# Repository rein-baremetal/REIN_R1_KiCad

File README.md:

# REIN_R1 Hardware Design (KiCad 8.0+)

Welcome to the **REIN_R1** open-source PCB hardware project, part of the [REIN Baremetal](https://github.com/rein-baremetal) organization!

REIN_R1 is a multi-controller embedded development board built specifically for baremetal development, dual-architecture real-time control, and high-reliability embedded system experiments.

---

## What Makes REIN_R1 Stand Out?

Unlike standard single-SoC maker boards or basic evaluation kits, REIN_R1 combines high-performance coprocessing, rich peripheral interfacing, and power flexibility on a single compact 4-layer PCB:

* **Dual Microcontroller Co-Processing Architecture:** Integrates dual MCUs on-board to allow simultaneous execution of dedicated real-time control loops alongside higher-level communication and application tasks.
* **On-Board High-Speed QSPI Storage:** Dedicated QSPI flash interface configured for fast memory-mapped execution (XIP) and rapid firmware assets retrieval.
* **Integrated Hardware USB Hub:** Built-in multi-port USB hub logic eliminates external debug adapters, handling simultaneous programming, serial telemetry, and peripheral expansion over a single USB-C connection.
* **Robust Multi-Rail Power Management:** Features protected power input, integrated buck regulation, dedicated low-noise analog power paths (`3V3_A`), and smart battery/line switching (`VSYS`, `VIN`, `VBAT`).
* **Flexible Expansion & Communication:** Exposes dedicated SPI, I2C, UART, ADC channels, and GPIO arrays directly mapped for fast baremetal driver development without hardware bottlenecks.

---

## Current PCB Status

- **Schematic (`REIN_R1.kicad_sch`):** 100% Complete & Verified
- **Footprints & Symbol Libraries:** Custom library included (`REIN.kicad_sym`, `REIN.pretty/`)
- **Component Placement (`REIN_R1.kicad_pcb`):** 100% Complete
- **Routing:** **In Progress (Help Needed!)**

We are seeking open-source collaborators, hardware engineers, and layout enthusiasts to help route the remaining traces and achieve a 100% routed board that passes KiCad DRC with zero errors.

---

## Technical Specifications & Constraints

- **Board Layers:** 4 Layers (`F.Cu`, `In1.Cu` - GND, `In2.Cu` - Power Fills, `B.Cu`)
- **Default Track Width:** 0.20 mm (8 mil)
- **Default Track Clearance:** 0.20 mm (8 mil)
- **Minimum SMD Clearance:** 0.05 mm
- **Via Drill/Size:** Standard 0.3 mm / 0.6 mm

### Critical Routing Guidelines
1. **USB Differential Pairs (`/USB_DM_*`, `/USB_DP_*`):** Keep trace lengths matched and route as 90 Ω differential pairs. Minimize layer changes.
2. **QSPI Lines (`/QSPI_SCLK_*`, `/QSPI_SD0_*` to `/QSPI_SD3_*`, `/QSPI_SS_*`):** Length-match bus signals where feasible between MCU and flash storage. Keep tracks direct.
3. **Oscillator Traces (`/XIN_*`, `/XOUT_*`):** Keep routes as short as possible and isolate with ground pour fills.
4. **Power & Ground (`/GND`, `/3V3`, `/5V`, `/VIN`, `/VSYS`):** Ensure `In1.Cu` and `In2.Cu` ground planes maintain continuous connectivity without creating starved thermal islands on power/GND pads. Recalculate filled zones (`Ctrl + B`) after routing.

---

## How to Collaborate & Route

You can participate using either **KiCad PCB Editor** or **Freerouting**:

### Option A: Interactive Routing in KiCad
1. Clone or fork this repository:
   ```bash
   git clone https://github.com/rein-baremetal/REIN_R1_KiCad.git

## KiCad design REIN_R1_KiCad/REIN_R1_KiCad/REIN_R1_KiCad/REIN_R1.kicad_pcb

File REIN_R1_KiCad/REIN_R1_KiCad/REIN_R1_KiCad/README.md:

## Files
REIN_R1.kicad_pro / .kicad_sch / .kicad_pcb, REIN.kicad_sym (+ sym-lib-table), REIN.pretty (+ fp-lib-table), BOM, net table, GPIO map, tools/gen.py

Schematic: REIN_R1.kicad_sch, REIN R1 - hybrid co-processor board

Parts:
BT1: CR1220; BatteryHolder_Keystone_3034_1x20mm
C1, C4, C5, C11, C15, C18, C19, C20, C21, C22, C23, C24, C25, C26, C27, C30, C31, C34, C35, C36, C37, C38, C39, C40, C41, C42, C43, C46, C47, C49, C54, C56, C57, C58, C59, C60, C62, C63, C64, C65, C66: 100n; C_0402_1005Metric
C2, C3, C7, C8, C9, C10, C12, C51, C55: 10u; C_0402_1005Metric
C6, C13, C14, C48: 22u; C_0402_1005Metric
C16, C17, C32, C33: 15p; C_0402_1005Metric
C28, C29, C44, C45, C50, C52, C53, C61: 1u; C_0402_1005Metric
D1: SMBJ24A; D_SMB
D2: SMBJ33A; D_SMB
D3, D4: SS34; D_SMA
D5, D6, D7: SS14; D_SOD-123
D8: CHG (red); LED_0603_1608Metric
D9: PWR (green); LED_0603_1608Metric
D10: BT / USER (blue); LED_0603_1608Metric
DZ1: BZX84-10V; D_SOD-123
F1: PTC 2A; Fuse_1206_3216Metric
FB1: Ferrite 600R; R_0402_1005Metric
J1: USB-C (HRO TYPE-C-31-M-12); USB_C_Receptacle_HRO_TYPE-C-31-M-12
J2: DC IN 6-36V; TerminalBlock_bornier-2_P5.08mm
J3: LiPo (JST-PH); JST_PH_S2B-PH-SM4-TB_1x02-1MP_P2.00mm_Horizontal
J4: microSD (Hirose DM3AT); microSD_HC_Hirose_DM3AT-SF-PEJM5
J5: OLED 0.91in (GND VCC SCL SDA); PinHeader_1x04_P2.54mm_Vertical
J6, J7: Qwiic (SH 4-pin); JST_SH_SM04B-SRSS-TB_1x04-1MP_P1.00mm_Horizontal
J8: Grove I2C (PH 4-pin); JST_PH_B4B-PH-K_1x04_P2.00mm_Vertical
J9: Pi 40-pin HAT socket; PinSocket_2x20_P2.54mm_Vertical
J10: EEPROM WP jumper (short = writable); PinHeader_1x02_P2.54mm_Vertical
J11: SWD (CLK DIO GND RUN 3V3); PinHeader_1x05_P2.54mm_Vertical
J12: Debug UART (GND TX RX); PinHeader_1x03_P2.54mm_Vertical
J13: ESP UART (GND TX RX 3V3); PinHeader_1x04_P2.54mm_Vertical
J14: Breadboard RP2040 5V I/O (22-27, 5V, GND); PinHeader_1x08_P2.54mm_Vertical
J15: Breadboard ESP32 5V I/O 1-8; PinHeader_1x08_P2.54mm_Vertical
J16: Breadboard power (5V 3V3 GND GND); PinHeader_1x04_P2.54mm_Vertical
J17: ADC in (AIN0-3, GND, 3V3_A); PinHeader_1x06_P2.54mm_Vertical
J18: DAC out (AOUT, GND); PinHeader_1x02_P2.54mm_Vertical
L1: 10u; L_1210_3225Metric
L2: 2.2u; L_Taiyo-Yuden_NR-40xx
Q1: P-MOSFET 40V (reverse protect); SOT-23
R1, R2: 5.1k; R_0402_1005Metric; not fitted
R3, R5, R13, R14: 100k; R_0402_1005Metric
R4: 732k; R_0402_1005Metric
R6: 2k; R_0402_1005Metric
R7, R10, R11, R12, R19, R20, R27, R33, R34, R35, R36: 1k; R_0402_1005Metric
R8: 1M; R_0402_1005Metric
R9: 221k; R_0402_1005Metric
R15, R16: 2.2k; R_0402_1005Metric
R17, R18, R25, R26, R28, R29, R30, R31, R32, R40, R41: 10k; R_0402_1005Metric
R21, R22, R23, R24: 27R; R_0402_1005Metric
R37: 100R; R_0402_1005Metric
R38, R39: 4.7k; R_0402_1005Metric
RSH1: 20m shunt; R_1206_3216Metric
SW1, SW3: BOOTSEL; SW_SPST_TL3342
SW2: RESET; SW_SPST_TL3342
SW4: PROBE RESET; SW_SPST_TL3342
SW5: ESP RESET; SW_SPST_TL3342
SW6: ESP BOOT; SW_SPST_TL3342
U1, U3: RP2040; QFN-56-1EP_7x7mm_P0.4mm_EP3.2x3.2mm
U2: W25Q128JVSIQ; SOIC-8_5.23x5.23mm_P1.27mm
U4: W25Q16JV; SOIC-8_5.23x5.23mm_P1.27mm
U5: ESP32-S3-WROOM-1-N8; ESP32-S3-WROOM-1
U7: Wide-in buck 5V (TPS54202-class); SOT-23-6
U8: INA226AIDGSR; VSSOP-10_3x3mm_P0.5mm
U9: MCP73831T-2ACI/OT; SOT-23-5
U10: MAX17048G+T10; DFN-8-1EP_2x2mm_P0.5mm_EP0.7x1.3mm
U11: TLV62569DBV; SOT-23-5
U12: REF3033 (3.3V ref); SOT-23
U13: ADS1115IDGSR; VSSOP-10_3x3mm_P0.5mm
U14: MCP4725A1T-E/CH; SOT-23-6
U15: ATECC608B-SSHDA; SOIC-8_3.9x4.9mm_P1.27mm
U16: DS3231SN#; SOIC-16W_7.5x10.3mm_P1.27mm
U17: USB2.0 4-port hub (CH334-class); QFN-24-1EP_4x4mm_P0.5mm_EP2.6x2.6mm
U18: STUSB4500 (QFN-24); QFN-24-1EP_4x4mm_P0.5mm_EP2.6x2.6mm
U19: USBLC6-2SC6; SOT-23-6
U20: TPS22918 (Qwiic switch); SOT-23-6
U21: CAT24C32WI (HAT ID EEPROM); SOIC-8_3.9x4.9mm_P1.27mm
U22, U23: TXS0108EPWR; TSSOP-20_4.4x6.5mm_P0.65mm
Y1, Y2: 12MHz; Crystal_SMD_3225-4Pin_3.2x2.5mm

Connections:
/1V1_P: C42.1, C43.1, C45.1, U3.23 (DVDD), U3.45 (VREG_VOUT), U3.50 (DVDD)
/1V1_T: C26.1, C27.1, C29.1, U1.23 (DVDD), U1.45 (VREG_VOUT), U1.50 (DVDD)
/3V3: C1.1, C5.1, C13.1, C14.1, C15.1, C18.1, C19.1, C20.1, C21.1, C22.1, C23.1, C24.1, C25.1, C28.1, C31.1, C34.1, C35.1, C36.1, C37.1, C38.1, C39.1, C40.1, C41.1, C44.1, C46.1, C47.1, C48.1, C49.1, C51.1, C57.1, C58.1, C60.1, C62.1, C63.1, C65.1, FB1.1, J4.4 (VDD), J5.2 (VCC), J11.5 (3V3), J13.4 (3V3), J16.2 (3V3), L2.2, R8.1, R10.1, R15.2, R16.2, R17.2, R18.2, R25.1, R26.1, R28.2, R29.2, R30.2, R31.2, R32.2, R40.2, R41.2, U1.1 (IOVDD), U1.10 (IOVDD), U1.22 (IOVDD), U1.33 (IOVDD), U1.42 (IOVDD), U1.43 (ADC_AVDD), U1.44 (VREG_VIN), U1.48 (USB_VDD), U1.49 (IOVDD), U2.8 (VCC), U3.1 (IOVDD), U3.10 (IOVDD), U3.22 (IOVDD), U3.33 (IOVDD), U3.42 (IOVDD), U3.43 (ADC_AVDD), U3.44 (VREG_VIN), U3.48 (USB_VDD), U3.49 (IOVDD), U4.8 (VCC), U5.2 (3V3), U8.6 (VS), U15.8 (VCC), U16.2 (VCC), U17.11 (VDD33), U18.11 (VDD), U20.1 (VIN), U21.8 (VCC), U22.2 (VCCA), U23.2 (VCCA)
/3V3_A: C55.1, C56.1, FB1.2, J17.6 (3V3A), U13.8 (VDD)
/5V: C7.1, C8.1, C9.1, C64.1, C66.1, D5.2 (A), D7.1 (K), J14.7 (5V), J16.1 (5V), R7.1, RSH1.2, U8.8 (VBUS), U8.9 (IN-), U9.4 (VDD), U22.19 (VCCB), U23.19 (VCCB)
/5V_BUCK: C6.1, F1.1, L1.2, R4.1
/5V_F: F1.2, RSH1.1, U8.10 (IN+)
/AIN0: R33.2, U13.4 (AIN0)
/AIN0_H: J17.1 (AIN0), R33.1
/AIN1: R34.2, U13.5 (AIN1)
/AIN1_H: J17.2 (AIN1), R34.1
/AIN2: R35.2, U13.6 (AIN2)
/AIN2_H: J17.3 (AIN2), R35.1
/AIN3: R36.2, U13.7 (AIN3)
/AIN3_H: J17.4 (AIN3), R36.1
/AOUT_H: J18.1 (AOUT), R37.2
/BB_22: J14.1 (IO22), U22.20 (B1)
/BB_23: J14.2 (IO23), U22.18 (B2)
/BB_24: J14.3 (IO24), U22.17 (B3)
/BB_25: J14.4 (IO25), U22.16 (B4)
/BB_26: J14.5 (IO26), U22.15 (B5)
/BB_27: J14.6 (IO27), U22.14 (B6)
/BE_1: J15.1 (E1), U23.20 (B1)
/BE_2: J15.2 (E2), U23.18 (B2)
/BE_3: J15.3 (E3), U23.17 (B3)
/BE_4: J15.4 (E4), U23.16 (B4)
/BE_5: J15.5 (E5), U23.15 (B5)
/BE_6: J15.6 (E6), U23.14 (B6)
/BE_7: J15.7 (E7), U23.13 (B7)
/BE_8: J15.8 (E8), U23.12 (B8)
/BK3_FB: R8.2, R9.1, U11.5 (FB)
/BK3_SW: L2.1, U11.3 (SW)
/BK5_BST: C4.1, U7.6 (BST)
/BK5_FB: R4.2, R5.1, U7.4 (FB)
/BK5_SW: C4.2, L1.1, U7.2 (SW)
/BOOTR_P: R20.2, SW3.1
/BOOTR_T: R12.2, SW1.1
/CC1: J1.A5, R1.1, U18.1 (CC1)
/CC2: J1.B5, R2.1, U18.2 (CC2)
/CHG_LED_A: D8.2 (A), R7.2
/CHG_PROG: R6.1, U9.5 (PROG)
/CHG_STAT: D8.1 (K), U9.1 (STAT)
/DAC_OUT: R37.1, U14.1 (VOUT)
/DBG_RX: J12.3 (RX), U1.3 (GPIO1), U3.6 (GPIO4)
/DBG_TX: J12.2 (TX), U1.2 (GPIO0), U3.7 (GPIO5)
/EE_WP: J10.1 (WP), R40.1, U21.7 (WP)
/ESP_B1: U5.4 (IO4), U23.1 (A1)
/ESP_B2: U5.5 (IO5), U23.3 (A2)
/ESP_B3: U5.6 (IO6), U23.4 (A3)
/ESP_B4: U5.7 (IO7), U23.5 (A4)
/ESP_B5: U5.8 (IO15), U23.6 (A5)
/ESP_B6: U5.9 (IO16), U23.7 (A6)
/ESP_B7: U5.10 (IO17), U23.8 (A7)
/ESP_B8: U5.11 (IO18), U23.9 (A8)
/ESP_CS: U1.28 (GPIO17), U5.18 (IO10)
/ESP_DRDY: U1.18 (GPIO15), U5.17 (IO9)
/ESP_EN: C50.1, R25.2, SW5.1, U1.31 (GPIO20), U5.3 (EN)
/ESP_HS: U1.17 (GPIO14), U5.22 (IO14)
/ESP_IO0: R26.2, SW6.1, U1.32 (GPIO21), U5.27 (IO0)
/ESP_MISO: U1.27 (GPIO16), U5.21 (IO13)
/ESP_MOSI: U1.30 (GPIO19), U5.19 (IO11)
/ESP_RXD0: J13.3 (RX), U5.36 (RXD0_IO44)
/ESP_SCK: U1.29 (GPIO18), U5.20 (IO12)
/ESP_TXD0: J13.2 (TX), U5.37 (TXD0_IO43)
/GND: BT1.2 (-), C1.2, C2.2, C3.2, C5.2, C6.2, C7.2, C8.2, C9.2, C10.2, C11.2, C12.2, C13.2, C14.2, C15.2, C16.2, C17.2, C18.2, C19.2, C20.2, C21.2, C22.2, C23.2, C24.2, C25.2, C26.2, C27.2, C28.2, C29.2, C30.2, C31.2, C32.2, C33.2, C34.2, C35.2, C36.2, C37.2, C38.2, C39.2, C40.2, C41.2, C42.2, C43.2, C44.2, C45.2, C46.2, C47.2, C48.2, C49.2, C50.2, C51.2, C52.2, C53.2, C54.2, C55.2, C56.2, C57.2, C58.2, C59.2, C60.2, C61.2, C62.2, C63.2, C64.2, C65.2, C66.2, D1.2 (A), D2.2 (A), D9.1 (K), D10.1 (K), J1.A1, J1.A12, J1.B1, J1.B12, J1.S1, J2.2 (GND), J3.2 (-), J3.MP, J4.6 (VSS), J4.10 (SH1), J4.11 (SH2), J5.1 (GND), J6.1 (GND), J6.MP, J7.1 (GND), J7.MP, J8.4 (GND), J9.6, J9.9, J9.14, J9.20, J9.25, J9.30, J9.34, J9.39, J10.2 (GND), J11.3 (GND), J12.1 (GND), J13.1 (GND), J14.8 (GND), J16.3 (GND), J16.4 (GND), J17.5 (GND), J18.2 (GND), R1.2, R2.2, R3.2, R5.2, R6.2, R9.2, R14.2, SW1.2, SW2.2, SW3.2, SW4.2, SW5.2, SW6.2, U1.19 (TESTEN), U1.57 (GND), U2.4 (GND), U3.19 (TESTEN), U3.57 (GND), U4.4 (GND), U5.1 (GND), U5.40 (GND), U5.41 (GND_EP), U7.1 (GND), U8.1 (A1), U8.2 (A0), U8.7 (GND), U9.2 (VSS), U10.3 (GND), U10.4 (QSTRT), U10.8 (CTG), U10.9 (EP), U11.2 (GND), U12.3 (GND), U13.1 (ADDR), U13.3 (GND), U14.2 (VSS), U14.6 (A0), U15.4 (GND), U16.13 (GND), U17.24 (GND), U17.25 (EP), U18.8 (ADDR0), U18.9 (ADDR1), U18.10 (RESET), U18.24 (GND), U18.25 (EP), U19.2 (GND), U20.2 (GND), U21.1 (A0), U21.2 (A1), U21.3 (A2), U21.4 (VSS), U22.11 (GND), U23.11 (GND), Y1.2 (GND), Y1.4 (GND), Y2.2 (GND), Y2.4 (GND)
/HUB_DM1: R24.1, U17.4 (DM1)
/HUB_DM2: R22.1, U17.6 (DM2)
/HUB_DP1: R23.1, U17.3 (DP1)
/HUB_DP2: R21.1, U17.5 (DP2)
/I2CA_SCL: J5.3 (SCL), R16.1, U1.7 (GPIO5), U8.5 (SCL), U10.6 (SCL), U13.10 (SCL), U14.5 (SCL), U15.6 (SCL), U16.16 (SCL), U18.6 (SCL)
/I2CA_SDA: J5.4 (SDA), R15.1, U1.6 (GPIO4), U8.4 (SDA), U10.5 (SDA), U13.9 (SDA), U14.4 (SDA), U15.5 (SDA), U16.15 (SDA), U18.5 (SDA)
/I2CQ_SCL: J6.4 (SCL), J7.4 (SCL), J8.1 (SCL), R39.1, U1.5 (GPIO3)
/I2CQ_SDA: J6.3 (SDA), J7.3 (SDA), J8.2 (SDA), R38.1, U1.4 (GPIO2)
/ID_SC: J9.28, U21.6 (SCL)
/ID_SD: J9.27, U21.5 (SDA)
/INT_PWR: R17.1, U1.8 (GPIO6), U8.3 (ALERT), U10.7 (ALRT), U18.7 (ALERT)
/LED_USR: R27.1, U5.38 (IO2)
/LED_USR_A: D10.2 (A), R27.2
/PI_5V: D7.2 (A), J9.2, J9.4
/PI_CE0: J9.24, U1.16 (GPIO13)
/PI_MISO: J9.21, U1.14 (GPIO11)
/PI_MOSI: J9.19, U1.15 (GPIO12)
/PI_RXD: J9.10, U1.11 (GPIO8)
/PI_SCLK: J9.23, U1.13 (GPIO10)
/PI_TXD: J9.8, U1.12 (GPIO9)
/PWR_LED_A: D9.2 (A), R10.2
/Q1_G: DZ1.2 (A), Q1.1 (G), R3.1
/Q3V3: C61.1, J6.2 (3V3), J7.2 (3V3), J8.3 (VCC), R38.2, R39.2, U20.6 (VOUT)
/QSPI_SCLK_P: U3.52 (QSPI_SCLK), U4.6 (CLK)
/QSPI_SCLK_T: U1.52 (QSPI_SCLK), U2.6 (CLK)
/QSPI_SD0_P: U3.53 (QSPI_SD0), U4.5 (DI/IO0)
/QSPI_SD0_T: U1.53 (QSPI_SD0), U2.5 (DI/IO0)
/QSPI_SD1_P: U3.55 (QSPI_SD1), U4.2 (DO/IO1)
/QSPI_SD1_T: U1.55 (QSPI_SD1), U2.2 (DO/IO1)
/QSPI_SD2_P: U3.54 (QSPI_SD2), U4.3 (WP#/IO2)
/QSPI_SD2_T: U1.54 (QSPI_SD2), U2.3 (WP#/IO2)
/QSPI_SD3_P: U3.51 (QSPI_SD3), U4.7 (HOLD#/IO3)
/QSPI_SD3_T: U1.51 (QSPI_SD3), U2.7 (HOLD#/IO3)
/QSPI_SS_P: R20.1, U3.56 (QSPI_SS), U4.1 (CS#)
/QSPI_SS_T: R12.1, U1.56 (QSPI_SS), U2.1 (CS#)
/QWIIC_EN: U1.40 (GPIO28_ADC2), U20.3 (ON)
/RP_IO22: U1.34 (GPIO22), U22.1 (A1)
/RP_IO23: U1.35 (GPIO23), U22.3 (A2)
/RP_IO24: U1.36 (GPIO24), U22.4 (A3)
/RP_IO25: U1.37 (GPIO25), U22.5 (A4)
/RP_IO26: U1.38 (GPIO26_ADC0), U22.6 (A5)
/RP_IO27: U1.39 (GPIO27_ADC1), U22.7 (A6)
/RTC_INT: R18.1, U1.9 (GPIO7), U16.3 (INT#/SQW)
/RTC_VBAT: BT1.1 (+), C59.1, U16.14 (VBAT)
/RUN_P: SW4.1, U3.26 (RUN)
/RUN_T: J11.4 (RUN), SW2.1, U1.26 (RUN), U3.3 (GPIO1)
/SD_CLK: J4.5 (CLK), U5.33 (IO40)
/SD_CMD: J4.3 (CMD), R32.1, U5.32 (IO39)
/SD_D0: J4.7 (DAT0), R28.1, U5.34 (IO41)
/SD_D1: J4.8 (DAT1), R29.1, U5.35 (IO42)
/SD_D2: J4.1 (DAT2), R30.1, U5.31 (IO38)
/SD_D3: J4.2 (DAT3/CD), R31.1, U5.23 (IO21)
/SWCLK: J11.1 (SWCLK), U1.24 (SWCLK), U3.4 (GPIO2)
/SWDIO: J11.2 (SWDIO), U1.25 (SWD), U3.5 (GPIO3)
/TXS_OE: R41.1, U22.10 (OE), U23.10 (OE)
/USB_DM_C: J1.A7, J1.B7, U17.2 (UP_DM), U19.3 (IO2), U19.4 (IO2b)
/USB_DP_C: J1.A6, J1.B6, U17.1 (UP_DP), U19.1 (IO1), U19.6 (IO1b)
/USB_E_DM: U5.13 (IO19_USB_DM), U17.8 (DM3)
/USB_E_DP: U5.14 (IO20_USB_DP), U17.7 (DP3)
/USB_P_DM: R22.2, U3.46 (USB_DM)
/USB_P_DP: R21.2, U3.47 (USB_DP)
/USB_T_DM: R24.2, U1.46 (USB_DM)
/USB_T_DP: R23.2, U1.47 (USB_DP)
/VBAT: C10.1, C11.1, D6.2 (A), J3.1 (+), U9.3 (VBAT), U10.1 (CELL), U10.2 (VDD)
/VBUS: D1.1 (K), D3.2 (A), J1.A4, J1.A9, J1.B4, J1.B9, U17.12 (VBUS_DET), U18.3 (VBUS_SENSE), U19.5 (VBUS)
/VDC_PROT: D4.2 (A), DZ1.1 (K), Q1.2 (S)
/VDC_RAW: D2.1 (K), J2.1 (VDC+), Q1.3 (D)
/VIN: C2.1, C3.1, D3.1 (K), D4.1 (K), U7.3 (VIN), U7.5 (EN)
/VREF_3V3: C53.1, C54.1, U12.2 (VOUT), U14.3 (VDD)
/VSYS: C12.1, C52.1, D5.1 (K), D6.1 (K), R13.1, U11.1 (EN), U11.4 (VIN), U12.1 (VIN)
/VSYS_SENSE: C30.1, R13.2, R14.1, U1.41 (GPIO29_ADC3)
/XIN_P: C32.1, U3.20 (XIN), Y2.1 (XIN)
/XIN_T: C16.1, U1.20 (XIN), Y1.1 (XIN)
/XOUT_P: R19.1, U3.21 (XOUT)
/XOUT_R_P: C33.1, R19.2, Y2.3 (XOUT)
/XOUT_R_T: C17.1, R11.2, Y1.3 (XOUT)
/XOUT_T: R11.1, U1.21 (XOUT)

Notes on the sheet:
1 USB-C + PD + hub
2 Power input + 5V
3 Charger, fuel gauge, 3V3
4 RP2040 target (main MCU)
5 RP2040 debug probe
6 USB hub + ESD
7 ESP32-S3 + microSD
8 Analog + secure + RTC
9 Bus A devices, Qwiic/Grove
10 Pi 5 HAT header + debug headers
11 Breadboard / level shifters
12 Power flags

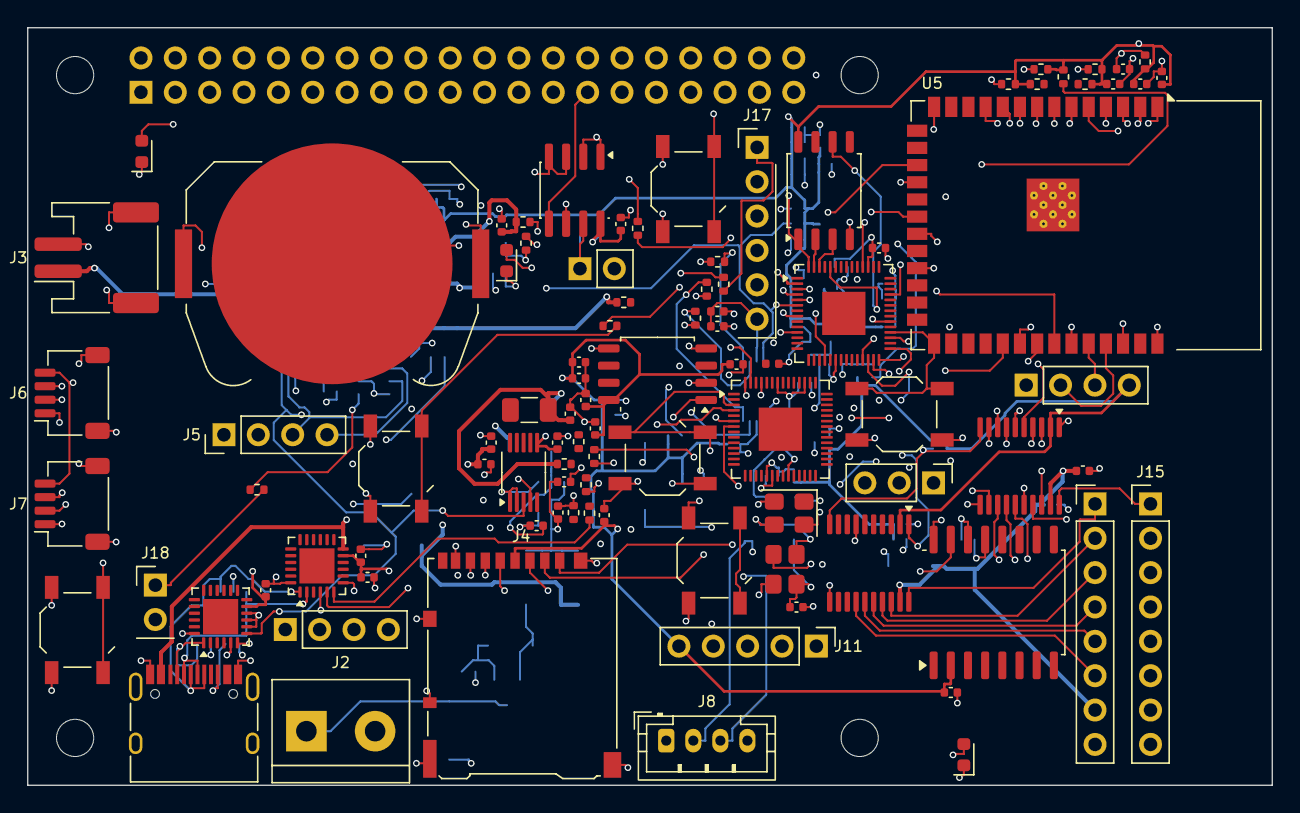
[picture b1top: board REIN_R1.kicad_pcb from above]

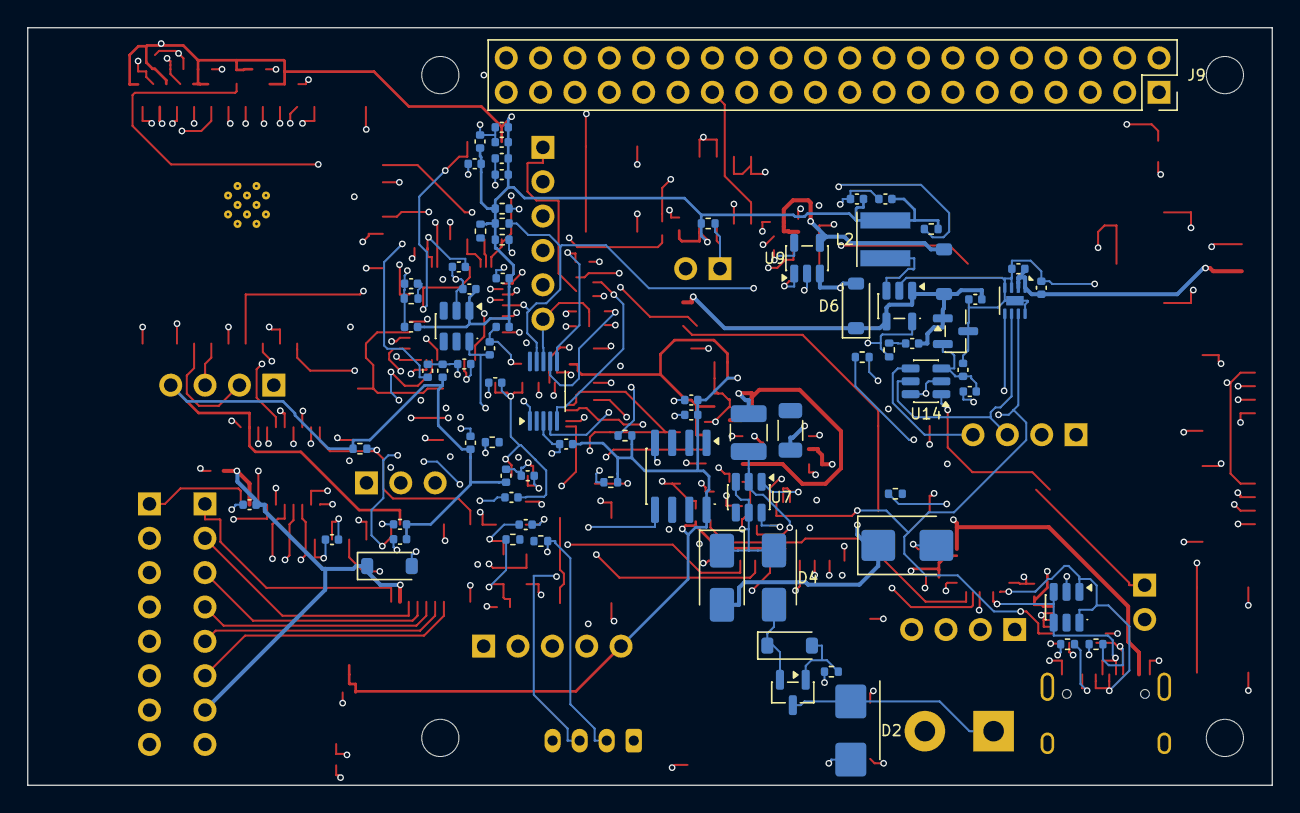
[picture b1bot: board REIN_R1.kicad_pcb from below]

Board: 4 copper layers, 92.0 x 56.0 mm, 177 parts (79 on the bottom side), 142 nets.

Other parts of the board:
H1, H2, H3, H4: MountingHole; MountingHole_2.75mm_M2.5_HAT

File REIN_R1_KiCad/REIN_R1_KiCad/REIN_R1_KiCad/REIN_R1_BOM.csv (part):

Ref,Value,Footprint,DNP,Confidence,Note
J1,USB-C (HRO TYPE-C-31-M-12),REIN:USB_C_Receptacle_HRO_TYPE-C-31-M-12,,ok,
R1,5.1k,Resistor_SMD:R_0402_1005Metric,yes,ok,Fit ONLY if PD controller U18 is removed
R2,5.1k,Resistor_SMD:R_0402_1005Metric,yes,ok,Fit ONLY if PD controller U18 is removed
D1,SMBJ24A,Diode_SMD:D_SMB,,ok,
U19,USBLC6-2SC6,Package_TO_SOT_SMD:SOT-23-6,,ok,
U18,STUSB4500 (QFN-24),Package_DFN_QFN:QFN-24-1EP_4x4mm_P0.5mm_EP2.6x2.6mm,,VERIFY,Generic pin order - replace with datasheet pinout
C1,100n,Capacitor_SMD:C_0402_1005Metric,,ok,
J2,DC IN 6-36V,REIN:TerminalBlock_bornier-2_P5.08mm,,ok,
D2,SMBJ33A,Diode_SMD:D_SMB,,ok,
Q1,P-MOSFET 40V (reverse protect),Package_TO_SOT_SMD:SOT-23,,ok,
R3,100k,Resistor_SMD:R_0402_1005Metric,,ok,
DZ1,BZX84-10V,Diode_SMD:D_SOD-123,,ok,
D3,SS34,Diode_SMD:D_SMA,,ok,
D4,SS34,Diode_SMD:D_SMA,,ok,
C2,10u,Capacitor_SMD:C_0402_1005Metric,,ok,
C3,10u,Capacitor_SMD:C_0402_1005Metric,,ok,
U7,Wide-in buck 5V (TPS54202-class),Package_TO_SOT_SMD:SOT-23-6,,VERIFY,Pin order from TPS54202 family - verify; check 36V rating of final part
C4,100n,Capacitor_SMD:C_0402_1005Metric,,ok,
L1,10u,Inductor_SMD:L_1210_3225Metric,,ok,
U8,INA226AIDGSR,REIN:VSSOP-10_3x3mm_P0.5mm,,ok,
C5,100n,Capacitor_SMD:C_0402_1005Metric,,ok,
R4,732k,Resistor_SMD:R_0402_1005Metric,,ok,
R5,100k,Resistor_SMD:R_0402_1005Metric,,ok,
C6,22u,Capacitor_SMD:C_0402_1005Metric,,ok,
F1,PTC 2A,Fuse:Fuse_1206_3216Metric,,ok,
RSH1,20m shunt,Resistor_SMD:R_1206_3216Metric,,ok,
D7,SS14,Diode_SMD:D_SOD-123,,ok,
C7,10u,Capacitor_SMD:C_0402_1005Metric,,ok,
C8,10u,Capacitor_SMD:C_0402_1005Metric,,ok,
U9,MCP73831T-2ACI/OT,Package_TO_SOT_SMD:SOT-23-5,,ok,
R6,2k,Resistor_SMD:R_0402_1005Metric,,ok,
C9,10u,Capacitor_SMD:C_0402_1005Metric,,ok,
C10,10u,Capacitor_SMD:C_0402_1005Metric,,ok,
R7,1k,Resistor_SMD:R_0402_1005Metric,,ok,
D8,CHG (red),LED_SMD:LED_0603_1608Metric,,ok,
J3,LiPo (JST-PH),Connector_JST:JST_PH_S2B-PH-SM4-TB_1x02-1MP_P2.00mm_Horizontal,,ok,
U10,MAX17048G+T10,REIN:DFN-8-1EP_2x2mm_P0.5mm_EP0.7x1.3mm,,VERIFY,Pin order from memory - verify against datasheet
C11,100n,Capacitor_SMD:C_0402_1005Metric,,ok,
D5,SS14,Diode_SMD:D_SOD-123,,ok,
D6,SS14,Diode_SMD:D_SOD-123,,ok,
C12,10u,Capacitor_SMD:C_0402_1005Metric,,ok,
U11,TLV62569DBV,Package_TO_SOT_SMD:SOT-23-5,,ok,
L2,2.2u,Inductor_SMD:L_Taiyo-Yuden_NR-40xx,,ok,
R8,1M,Resistor_SMD:R_0402_1005Metric,,ok,
R9,221k,Resistor_SMD:R_0402_1005Metric,,ok,
C13,22u,Capacitor_SMD:C_0402_1005Metric,,ok,
C14,22u,Capacitor_SMD:C_0402_1005Metric,,ok,
R10,1k,Resistor_SMD:R_0402_1005Metric,,ok,
D9,PWR (green),LED_SMD:LED_0603_1608Metric,,ok,
U1,RP2040,Package_DFN_QFN:QFN-56-1EP_7x7mm_P0.4mm_EP3.2x3.2mm,,ok,
U2,W25Q128JVSIQ,REIN:SOIC-8_5.23x5.23mm_P1.27mm,,ok,
C15,100n,Capacitor_SMD:C_0402_1005Metric,,ok,
Y1,12MHz,Crystal:Crystal_SMD_3225-4Pin_3.2x2.5mm,,ok,
R11,1k,Resistor_SMD:R_0402_1005Metric,,ok,
C16,15p,Capacitor_SMD:C_0402_1005Metric,,ok,
C17,15p,Capacitor_SMD:C_0402_1005Metric,,ok,
C18,100n,Capacitor_SMD:C_0402_1005Metric,,ok,
C19,100n,Capacitor_SMD:C_0402_1005Metric,,ok,
C20,100n,Capacitor_SMD:C_0402_1005Metric,,ok,
C21,100n,Capacitor_SMD:C_0402_1005Metric,,ok,
C22,100n,Capacitor_SMD:C_0402_1005Metric,,ok,
C23,100n,Capacitor_SMD:C_0402_1005Metric,,ok,
C24,100n,Capacitor_SMD:C_0402_1005Metric,,ok,
C25,100n,Capacitor_SMD:C_0402_1005Metric,,ok,
C26,100n,Capacitor_SMD:C_0402_1005Metric,,ok,
C27,100n,Capacitor_SMD:C_0402_1005Metric,,ok,
C28,1u,Capacitor_SMD:C_0402_1005Metric,,ok,
C29,1u,Capacitor_SMD:C_0402_1005Metric,,ok,
R12,1k,Resistor_SMD:R_0402_1005Metric,,ok,
SW1,BOOTSEL,Button_Switch_SMD:SW_SPST_TL3342,,ok,
SW2,RESET,Button_Switch_SMD:SW_SPST_TL3342,,ok,
R13,100k,Resistor_SMD:R_0402_1005Metric,,ok,
R14,100k,Resistor_SMD:R_0402_1005Metric,,ok,
C30,100n,Capacitor_SMD:C_0402_1005Metric,,ok,
R15,2.2k,Resistor_SMD:R_0402_1005Metric,,ok,
R16,2.2k,Resistor_SMD:R_0402_1005Metric,,ok,
R17,10k,Resistor_SMD:R_0402_1005Metric,,ok,
R18,10k,Resistor_SMD:R_0402_1005Metric,,ok,
U3,RP2040,Package_DFN_QFN:QFN-56-1EP_7x7mm_P0.4mm_EP3.2x3.2mm,,ok,
U4,W25Q16JV,REIN:SOIC-8_5.23x5.23mm_P1.27mm,,ok,
C31,100n,Capacitor_SMD:C_0402_1005Metric,,ok,
Y2,12MHz,Crystal:Crystal_SMD_3225-4Pin_3.2x2.5mm,,ok,
R19,1k,Resistor_SMD:R_0402_1005Metric,,ok,
C32,15p,Capacitor_SMD:C_0402_1005Metric,,ok,
C33,15p,Capacitor_SMD:C_0402_1005Metric,,ok,
C34,100n,Capacitor_SMD:C_0402_1005Metric,,ok,
C35,100n,Capacitor_SMD:C_0402_1005Metric,,ok,
C36,100n,Capacitor_SMD:C_0402_1005Metric,,ok,
C37,100n,Capacitor_SMD:C_0402_1005Metric,,ok,
C38,100n,Capacitor_SMD:C_0402_1005Metric,,ok,
C39,100n,Capacitor_SMD:C_0402_1005Metric,,ok,
C40,100n,Capacitor_SMD:C_0402_1005Metric,,ok,
C41,100n,Capacitor_SMD:C_0402_1005Metric,,ok,
C42,100n,Capacitor_SMD:C_0402_1005Metric,,ok,
C43,100n,Capacitor_SMD:C_0402_1005Metric,,ok,
C44,1u,Capacitor_SMD:C_0402_1005Metric,,ok,
C45,1u,Capacitor_SMD:C_0402_1005Metric,,ok,
R20,1k,Resistor_SMD:R_0402_1005Metric,,ok,
SW3,BOOTSEL,Button_Switch_SMD:SW_SPST_TL3342,,ok,
SW4,PROBE RESET,Button_Switch_SMD:SW_SPST_TL3342,,ok,
R21,27R,Resistor_SMD:R_0402_1005Metric,,ok,
R22,27R,Resistor_SMD:R_0402_1005Metric,,ok,
R23,27R,Resistor_SMD:R_0402_1005Metric,,ok,
R24,27R,Resistor_SMD:R_0402_1005Metric,,ok,
U17,USB2.0 4-port hub (CH334-class),Package_DFN_QFN:QFN-24-1EP_4x4mm_P0.5mm_EP2.6x2.6mm,,VERIFY,Generic pin order - replace with datasheet pinout of the chosen hub IC
C46,100n,Capacitor_SMD:C_0402_1005Metric,,ok,
C47,100n,Capacitor_SMD:C_0402_1005Metric,,ok,
U5,ESP32-S3-WROOM-1-N8,RF_Module:ESP32-S3-WROOM-1,,ok,
C48,22u,Capacitor_SMD:C_0402_1005Metric,,ok,
C49,100n,Capacitor_SMD:C_0402_1005Metric,,ok,
R25,10k,Resistor_SMD:R_0402_1005Metric,,ok,
C50,1u,Capacitor_SMD:C_0402_1005Metric,,ok,
SW5,ESP RESET,Button_Switch_SMD:SW_SPST_TL3342,,ok,
R26,10k,Resistor_SMD:R_0402_1005Metric,,ok,
SW6,ESP BOOT,Button_Switch_SMD:SW_SPST_TL3342,,ok,
R27,1k,Resistor_SMD:R_0402_1005Metric,,ok,
D10,BT / USER (blue),LED_SMD:LED_0603_1608Metric,,ok,
J4,microSD (Hirose DM3AT),REIN:microSD_HC_Hirose_DM3AT-SF-PEJM5,,VERIFY,"Pin names from memory; shield pins 10/11 to GND, DET unused"
R28,10k,Resistor_SMD:R_0402_1005Metric,,ok,
R29,10k,Resistor_SMD:R_0402_1005Metric,,ok,
R30,10k,Resistor_SMD:R_0402_1005Metric,,ok,
R31,10k,Resistor_SMD:R_0402_1005Metric,,ok,
R32,10k,Resistor_SMD:R_0402_1005Metric,,ok,
C51,10u,Capacitor_SMD:C_0402_1005Metric,,ok,
U12,REF3033 (3.3V ref),Package_TO_SOT_SMD:SOT-23,,VERIFY,Pin order generic - verify; VSYS must exceed ~3.4V for regulation
C52,1u,Capacitor_SMD:C_0402_1005Metric,,ok,
C53,1u,Capacitor_SMD:C_0402_1005Metric,,ok,
C54,100n,Capacitor_SMD:C_0402_1005Metric,,ok,
FB1,Ferrite 600R,Resistor_SMD:R_0402_1005Metric,,ok,
C55,10u,Capacitor_SMD:C_0402_1005Metric,,ok,
U13,ADS1115IDGSR,REIN:VSSOP-10_3x3mm_P0.5mm,,ok,
C56,100n,Capacitor_SMD:C_0402_1005Metric,,ok,
R33,1k,Resistor_SMD:R_0402_1005Metric,,ok,
R34,1k,Resistor_SMD:R_0402_1005Metric,,ok,
R35,1k,Resistor_SMD:R_0402_1005Metric,,ok,
R36,1k,Resistor_SMD:R_0402_1005Metric,,ok,
U14,MCP4725A1T-E/CH,Package_TO_SOT_SMD:SOT-23-6,,ok,
R37,100R,Resistor_SMD:R_0402_1005Metric,,ok,
U15,ATECC608B-SSHDA,Package_SO:SOIC-8_3.9x4.9mm_P1.27mm,,ok,
C57,100n,Capacitor_SMD:C_0402_1005Metric,,ok,
U16,DS3231SN#,Package_SO:SOIC-16W_7.5x10.3mm_P1.27mm,,ok,
C58,100n,Capacitor_SMD:C_0402_1005Metric,,ok,
BT1,CR1220,Battery:BatteryHolder_Keystone_3034_1x20mm,,ok,
C59,100n,Capacitor_SMD:C_0402_1005Metric,,ok,
J5,OLED 0.91in (GND VCC SCL SDA),Connector_PinHeader_2.54mm:PinHeader_1x04_P2.54mm_Vertical,,ok,
U20,TPS22918 (Qwiic switch),Package_TO_SOT_SMD:SOT-23-6,,VERIFY,Pin order generic - verify
C60,100n,Capacitor_SMD:C_0402_1005Metric,,ok,
C61,1u,Capacitor_SMD:C_0402_1005Metric,,ok,
R38,4.7k,Resistor_SMD:R_0402_1005Metric,,ok,
R39,4.7k,Resistor_SMD:R_0402_1005Metric,,ok,
J6,Qwiic (SH 4-pin),Connector_JST:JST_SH_SM04B-SRSS-TB_1x04-1MP_P1.00mm_Horizontal,,ok,
J7,Qwiic (SH 4-pin),Connector_JST:JST_SH_SM04B-SRSS-TB_1x04-1MP_P1.00mm_Horizontal,,ok,
J8,Grove I2C (PH 4-pin),Connector_JST:JST_PH_B4B-PH-K_1x04_P2.00mm_Vertical,,ok,
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
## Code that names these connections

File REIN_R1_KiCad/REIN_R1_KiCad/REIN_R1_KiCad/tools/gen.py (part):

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# ---- hub
R("HUB_DP1", "USB_T_DP", "27R", S_HUB); R("HUB_DM1", "USB_T_DM", "27R", S_HUB)
# note: probe series resistors above connect HUB_DP2/DM2 side
parts[-4].pins[0] = ("1", "1", "p", "HUB_DP2"); parts[-3].pins[0] = ("1", "1", "p", "HUB_DM2")
for p in parts:
    if p.pins and p.pins[0][3] in ("USB_P_DP_H", "USB_P_DM_H"):
        p.pins[0] = (p.pins[0][0], p.pins[0][1], "p", "HUB_DP2" if p.pins[0][3] == "USB_P_DP_H" else "HUB_DM2")
gen("U17", "USB_HUB_4P_GENERIC", "USB2.0 4-port hub (CH334-class)", FP["QFN24"],
    [("UP_DP", "p", "USB_DP_C"), ("UP_DM", "p", "USB_DM_C"), ("DP1", "p", "HUB_DP1"), ("DM1", "p", "HUB_DM1"),
     ("DP2", "p", "HUB_DP2"), ("DM2", "p", "HUB_DM2"), ("DP3", "p", "USB_E_DP"), ("DM3", "p", "USB_E_DM"),
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
# ---- analog / secure / RTC
gen("U12", "REF3033", "REF3033 (3.3V ref)", FP["SOT23"], [("VIN", "i", "VSYS"), ("VOUT", "p", "VREF_3V3"), ("GND", "i", "GND")],
    S_ANA, conf="VERIFY", note="Pin order generic - verify; VSYS must exceed ~3.4V for regulation")
decap("VSYS", S_ANA, 1, "1u"); decap("VREF_3V3", S_ANA, 1, "1u"); decap("VREF_3V3", S_ANA, 1, "100n")
add("FB1", "FB", "Ferrite 600R", FP["R"], [("1", "1", "p", "3V3"), ("2", "2", "p", "3V3_A")], S_ANA, hide_names=True)
decap("3V3_A", S_ANA, 1, "10u")
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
